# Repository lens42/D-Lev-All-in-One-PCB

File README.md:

# D-Lev-All-in-One-PCB
This integrates the excellent D-Lev digital theremin design at D-Lev.com into a single surface-mount PCB.

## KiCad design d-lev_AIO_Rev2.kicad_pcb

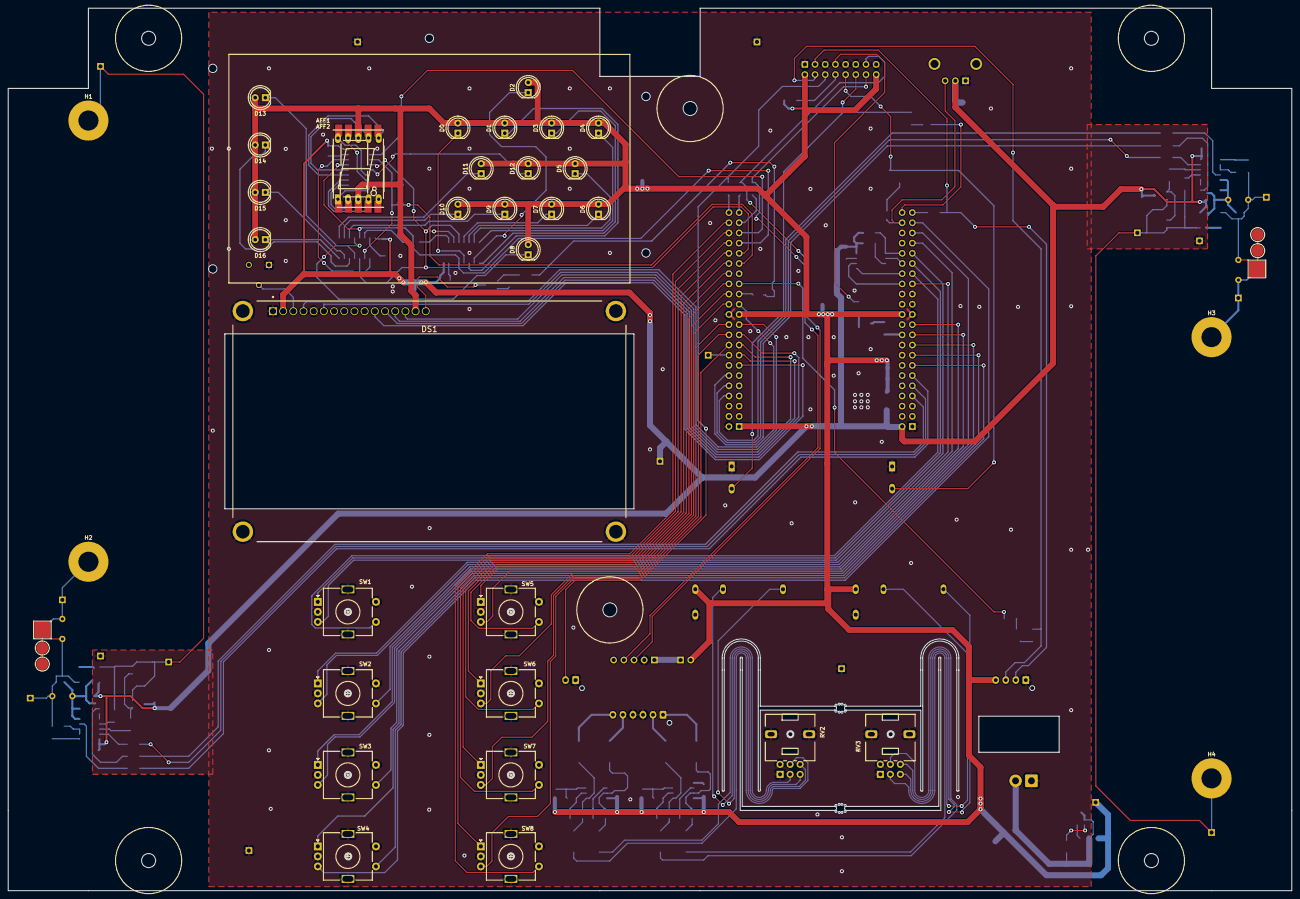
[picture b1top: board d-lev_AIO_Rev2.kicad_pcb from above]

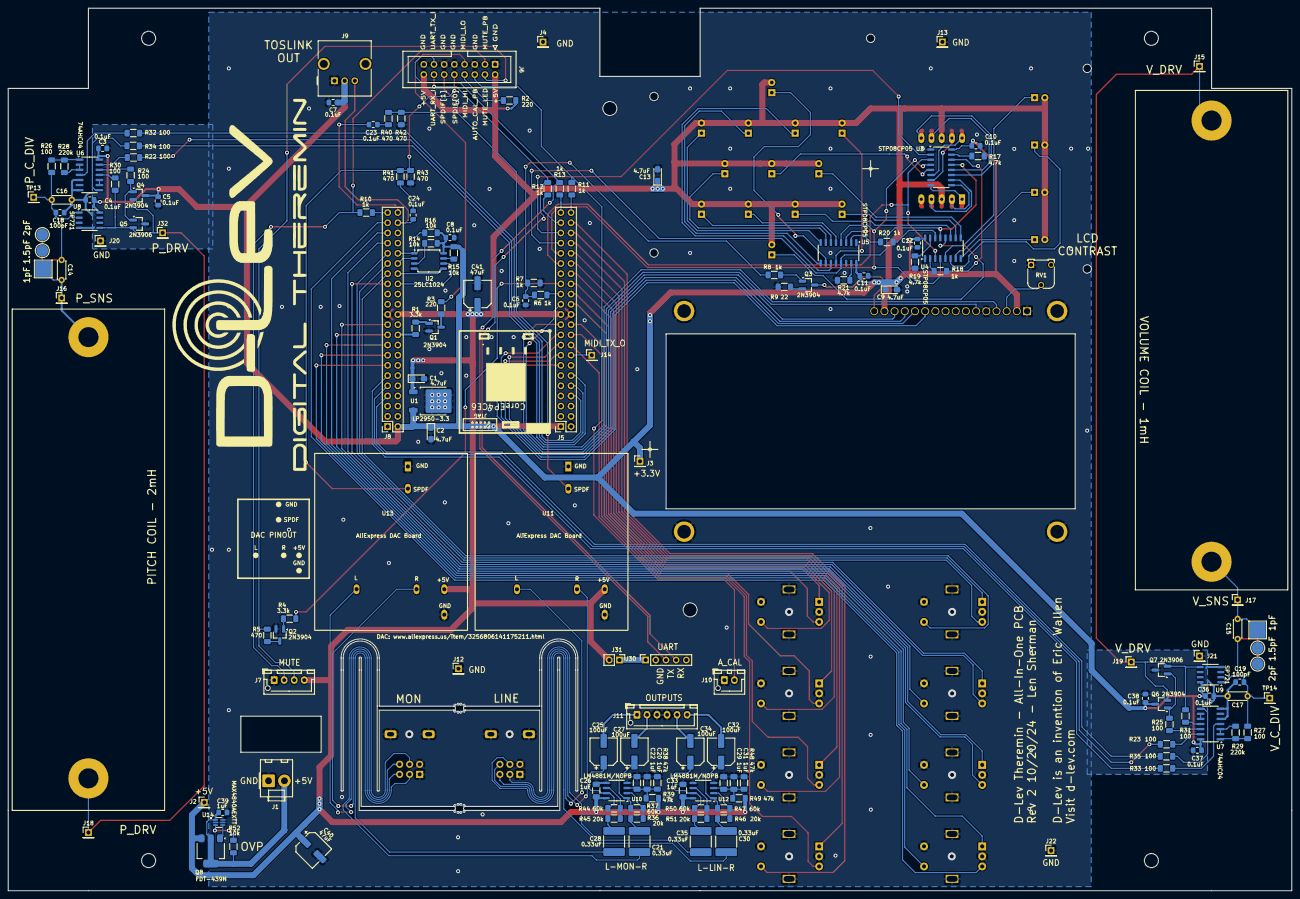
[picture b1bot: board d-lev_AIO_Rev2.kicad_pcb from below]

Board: 2 copper layers, 320.0 x 220.0 mm, 191 parts (149 on the bottom side), 165 nets.

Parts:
AFF1: LTS-6960HR; 7SEGMENT-LED__HDSM531_HDSM533_SMD
AFF2: LTS-6960HR; 7SegmentLED_LTS6760_LTS6780-centered
C1, C2, C9, C13: 4.7uF; CP_EIA-3216-18_Kemet-A_Pad1.58x1.35mm_HandSolder
C3, C4, C5, C6, C7, C8, C10, C11, C12, C23, C24, C36, C37, C38: 0.1uF; C_0805_2012Metric_Pad1.18x1.45mm_HandSolder
C14, C15: 1pF; C_Disc_D4.3mm_W1.9mm_P5.00mm
C16, C17: 100pF; C_Disc_D4.3mm_W1.9mm_P5.00mm
C18, C19: 100pF; C_0805_2012Metric_Pad1.18x1.45mm_HandSolder
C20, C22, C26, C29, C31, C33: 1uF; C_1206_3216Metric_Pad1.33x1.80mm_HandSolder
C21, C28, C30, C35: 0.33uF; C_2220_5750Metric_Pad1.97x5.40mm_HandSolder
C25, C27, C32, C34: 100uF; CP_Elec_6.3x7.7
C39: 1uF; C_0805_2012Metric_Pad1.18x1.45mm_HandSolder
C40, C41: 47uF; CP_Elec_6.3x7.7
D0, D1, D2, D3, D4, D5, D6, D7, D8, D9, D10, D11, D12, D13, D14, D15, D16: LED; LED_D5.0mm flush mounted
DS1: LCD-20X4B; LCD_LCD-20X4B
H1, H2, H3, H4: MountingHole_Pad; MountingHole_5mm_Pad
J1: Conn_01x02_Male; Molex_KK-396_A-41791-0002_1x02_P3.96mm_Vertical
J2, J3, J4, J12, J13, J22: Conn_01x01_Pin; PinHeader_1x01_P2.54mm_Vertical
J5, J8: Conn_02x22_Odd_Even; PinSocket_2x22_P2.54mm_Vertical
J6: Conn_02x08_Odd_Even; IDC-Header_2x08_P2.54mm_Vertical
J7: Conn_01x04_Pin; JST_XH_B4B-XH-AM_1x04_P2.50mm_Vertical
J9: TOSLINK_TX
J10: Conn_01x02_Pin; JST_XH_B2B-XH-AM_1x02_P2.50mm_Vertical
J11: Conn_01x06_Pin; JST_XH_B6B-XH-AM_1x06_P2.50mm_Vertical
J14, J15, J16, J17, J18, J19, J20, J21, J32: Conn_01x01_Male; PinHeader_1x01_P2.54mm_Vertical
J30: Conn_01x05_Pin; PinSocket_1x05_P2.54mm_Vertical
J31: Conn_01x02; PinHeader_1x02_P2.54mm_Vertical
Q1, Q2, Q3, Q4, Q6: 2N3904; SOT-23_Handsoldering
Q5, Q7: 2N3906; SOT-23_Handsoldering
Q8: FDT-439N; SOT-223-3_TabPin2
R1, R4: 3.3k; R_1206_3216Metric_Pad1.30x1.75mm_HandSolder
R2, R3: 220; R_1206_3216Metric_Pad1.30x1.75mm_HandSolder
R5, R40, R41, R42, R43: 470; R_1206_3216Metric_Pad1.30x1.75mm_HandSolder
R6, R7, R8, R10, R11, R12, R13, R18, R20: 1k; R_1206_3216Metric_Pad1.30x1.75mm_HandSolder
R9: 22; R_1206_3216Metric_Pad1.30x1.75mm_HandSolder
R14, R15, R16, R52: 10k; R_1206_3216Metric_Pad1.30x1.75mm_HandSolder
R17, R19, R21: 4.7k; R_1206_3216Metric_Pad1.30x1.75mm_HandSolder
R22, R23, R24, R25, R26, R27, R30, R31, R32, R33, R34, R35: 100; R_1206_3216Metric_Pad1.30x1.75mm_HandSolder
R28, R29: 220k; R_1206_3216Metric_Pad1.30x1.75mm_HandSolder
R36, R45, R46, R51: 20k; R_1206_3216Metric_Pad1.30x1.75mm_HandSolder
R37, R44, R47, R50: 60k; R_1206_3216Metric_Pad1.30x1.75mm_HandSolder
R38, R39, R48, R49: 47k; R_1206_3216Metric_Pad1.30x1.75mm_HandSolder
RV1: R_POT_US; Potentiometer_Runtron_RM-065_Vertical
RV2, RV3: 10k pot; Potentiometer_Alps_RK09L_Double_Vertical - recentered
SW1, SW2, SW3, SW4, SW5, SW6, SW7, SW8: RotaryEncoder_Switch_MP; RotaryEncoder_Alps_EC11E-Switch_Vertical_H20mm w 3D
TP1, TP2, TP3, TP4, TP5, TP6, TP9, TP10: TestPoint; TestPoint_Pad_D3.0mm
TP7, TP8, TP11, TP12: TestPoint; TestPoint_Pad_4.0x4.0mm
TP13, TP14: TestPoint; PinHeader_1x01_P2.54mm_Vertical
U1: LP2950-3.3; TO-252-2
U2: 25LC1024; SO-8_25LC1024_EEPROM
U3, U4, U5: STP08CP05; SO-16_3.9x9.9mm_P1.27mm
U6, U7: 74AHC04; SO-14_3.9x8.65mm_P1.27mm
U8, U9: SP721; SO-8_3.9x4.9mm_P1.27mm
U10, U12: LM4881M/NOPB; SO-8_3.9x4.9mm_P1.27mm
U11, U13: Audio DAC Brd
U14: MAX4840AEXTT; SOT65P210X110-6N
mouse-bite-1mm-slot, mouse-bite-1mm-slot#2: VAL**; mouse-bite-1mm-slot

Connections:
+3V3: C2.1, C3.1, C4.1, C5.1, C7.1, C8.1, C9.1, C10.1, C11.1, C12.1, C36.1, C37.1, C38.1, DS1.2 (VDD), J3.1, J5.1, J8.2, J9.2 (VCC), Q4.3 (C), Q6.3 (C), R14.2, R15.2, R16.1, U1.3 (VO), U2.8 (VCC), U3.16 (VDD), U4.16 (VDD), U5.16 (VDD), U6.14 (VCC), U7.14 (VCC), U8.8 (VCC), U9.8 (VCC)
+5V: AFF1.3 (C.A.), AFF1.8 (C.A.), AFF2.3 (C.A.), AFF2.8 (C.A.), C1.1, C13.1, C26.2, C33.2, C40.1, C41.1, D0.2 (A), D1.2 (A), D2.2 (A), D3.2 (A), D4.2 (A), D5.2 (A), D6.2 (A), D7.2 (A), D8.2 (A), D9.2 (A), D10.2 (A), D11.2 (A), D12.2 (A), D13.2 (A), D14.2 (A), D15.2 (A), D16.2 (A), DS1.15 (A), J2.1, J5.23, J6.2, J6.16, J7.4, J8.24, J31.2, Q8.3 (S), R2.2, R39.2, R49.2, U1.1 (VI), U10.8 (VDD), U11.5 (DC_5V), U12.8 (VDD), U13.5 (DC_5V)
/acal_pb: J6.6, J10.2, R11.1
/pb_mute_pu: J6.3, J7.2, R10.2
A: AFF1.7 (a), AFF2.7 (a), U3.12 (OUT7)
A0: J8.33, SW1.A
A1: J8.29, SW2.A
A2: J8.19, SW3.A
A3: J8.15, SW4.A
A4: J5.28, SW5.A
A5: J5.32, SW6.A
A6: J5.36, SW7.A
A7: J5.40, SW8.A
B: AFF1.6 (b), AFF2.6 (b), U3.11 (OUT6)
B0: J8.35, SW1.B
B1: J8.37, SW2.B
B2: J8.39, SW3.B
B3: J8.41, SW4.B
B4: J5.26, SW5.B
B5: J5.22, SW6.B
B6: J5.20, SW7.B
B7: J5.18, SW8.B
C: AFF1.4 (c), AFF2.4 (c), U3.10 (OUT5)
D: AFF1.2 (d), AFF2.2 (d), U3.9 (OUT4)
E: AFF1.1 (e), AFF2.1 (e), U3.8 (OUT3)
F: AFF1.9 (f), AFF2.9 (f), U3.7 (OUT2)
G: AFF1.10 (g), AFF2.10 (g), U3.6 (OUT1)
GND: C1.2, C2.2, C3.2, C4.2, C5.2, C6.2, C7.2, C8.2, C9.2, C10.2, C11.2, C12.2, C13.2, C16.2, C17.2, C18.2, C19.2, C20.1, C22.1, C26.1, C29.1, C31.1, C33.1, C36.2, C37.2, C38.2, C39.2, C40.2, C41.2, DS1.1 (VSS), DS1.5 (R/W), DS1.S1 (SHIELD), DS1.S2 (SHIELD), DS1.S3 (SHIELD), DS1.S4 (SHIELD), J1.1, J4.1, J5.2, J5.24, J6.1, J6.5, J6.9, J6.11, J6.15, J7.1, J8.1, J8.23, J9.1 (GND), J10.1, J11.3, J11.4, J12.1, J13.1, J20.1, J21.1, J22.1, J30.2, Q1.2 (E), Q2.2 (E), Q5.3 (C), Q7.3 (C), R7.2, R9.1, R17.2, R19.2, R21.2, R38.2, R42.2, R43.2, R48.2, RV1.1, RV2.1, RV2.4, RV2.MP (MountPin), RV3.1, RV3.4, RV3.MP (MountPin), SW1.C, SW1.MP, SW1.S2, SW2.C, SW2.MP, SW2.S2, SW3.C, SW3.MP, SW3.S2, SW4.C, SW4.MP, SW4.S2, SW5.C, SW5.MP, SW5.S2, SW6.C, SW6.MP, SW6.S2, SW7.C, SW7.MP, SW7.S2, SW8.C, SW8.MP, SW8.S2, U1.2 (GND), U2.4 (GND), U3.1 (GND), U4.1 (GND), U5.1 (GND), U6.5, U6.7 (GND), U7.5, U7.7 (GND), U8.4 (GND), U9.4 (GND), U10.4 (GND), U10.5 (SD), U11.1 (GND), U11.6 (GND), U12.4 (GND), U12.5 (SD), U13.1 (GND), U13.6 (GND), U14.2 (GND), U14.5 (NC), U14.6 (~EN)
LED0: D0.1 (K), U5.12 (OUT7)
LED1: D1.1 (K), U5.11 (OUT6)
LED2: D2.1 (K), U5.10 (OUT5)
LED3: D3.1 (K), U5.9 (OUT4)
LED4: D4.1 (K), U5.8 (OUT3)
LED5: D5.1 (K), U5.7 (OUT2)
LED6: D6.1 (K), U5.6 (OUT1)
LED7: D7.1 (K), U5.5 (OUT0)
LED8: D8.1 (K), U4.12 (OUT7)
LED9: D9.1 (K), U4.11 (OUT6)
LED10: D10.1 (K), U4.10 (OUT5)
LED11: D11.1 (K), U4.9 (OUT4)
LED12: D12.1 (K), U3.5 (OUT0)
LED13: D13.1 (K), U4.5 (OUT0)
LED14: D14.1 (K), U4.6 (OUT1)
LED15: D15.1 (K), U4.7 (OUT2)
LED16: D16.1 (K), U4.8 (OUT3)
LINE_L_AMP_IN: C30.2, RV2.5
LINE_L_DAC: RV2.6, U11.3 (LEFT_OUT)
LINE_R_AMP_IN: C35.1, RV2.2
LINE_R_DAC: RV2.3, U11.4 (RIGHT_OUT)
LIN_L_OUT: C32.2, J11.6
LIN_R_OUT: C34.2, J11.5
MON_L_AMP_IN: C21.2, RV3.5
MON_L_DAC: RV3.6, U13.3 (LEFT_OUT)
MON_L_OUT: C27.2, J11.2
MON_R_AMP_IN: C28.2, RV3.2
MON_R_DAC: RV3.3, U13.4 (RIGHT_OUT)
MON_R_OUT: C25.2, J11.1
unnamed: AFF1.5 (DP), AFF2.5 (DP)
unnamed: C6.1, R6.1, R7.1, R8.2
unnamed: C21.1, R36.2
unnamed: C23.2, R40.2
unnamed: C24.2, R41.2
unnamed: C28.1, R45.1
unnamed: C30.1, R46.2
unnamed: C35.2, R51.1
unnamed: C39.1, J1.2, Q8.2 (D), R52.2, U14.1 (IN)
unnamed: C14.1, H3.1, J16.1, TP7.1
unnamed: C15.1, H2.1, J17.1, TP8.1
unnamed: J30.1, J31.1
unnamed: J6.13, J30.3, R13.2
unnamed: J6.14, J30.4, R12.1
unnamed: Q1.1 (B), R1.1
unnamed: Q1.3 (C), R3.2
unnamed: Q2.1 (B), R4.1
unnamed: Q2.3 (C), R5.2
unnamed: Q3.1 (B), R8.1
unnamed: Q3.2 (E), R9.2
unnamed: Q4.1 (B), Q5.1 (B), R24.1
unnamed: Q6.1 (B), Q7.1 (B), R25.1
unnamed: Q8.1 (G), U14.4 (GATE)
unnamed: R22.1, U6.13
unnamed: R23.1, U7.13
unnamed: R24.2, U6.12
unnamed: R25.2, U7.12
unnamed: R26.1, R28.2, U6.1
unnamed: R27.1, R29.2, U7.1
unnamed: R28.1, U6.2, U6.3
unnamed: R29.1, U7.2, U7.3
unnamed: R30.1, U6.11
unnamed: R31.1, U7.11
unnamed: R32.2, U6.4
unnamed: R33.2, U7.4
unnamed: R34.2, U6.8
unnamed: R35.2, U7.8
unnamed: R15.1, U2.7 (~HOLD)
unnamed: R14.1, U2.3 (~WP)
unnamed: R17.1, U3.15 (R-EXT)
unnamed: R18.2, U3.14 (SDO)
unnamed: R19.1, U4.15 (R-EXT)
unnamed: R18.1, U4.2 (SDI)
unnamed: R20.2, U4.14 (SDO)
unnamed: R21.1, U5.15 (R-EXT)
unnamed: R20.1, U5.2 (SDI)
unnamed: U6.9, U6.10
unnamed: U7.9, U7.10
unnamed: C20.2, C22.2, R38.1, R39.1, U10.3 (BYPASS)
unnamed: R36.1, R37.2, U10.2 (IN_A)
unnamed: R44.2, R45.2, U10.6 (IN_B)
unnamed: C27.1, R37.1, U10.1 (OUT_A)
unnamed: C25.1, R44.1, U10.7 (OUT_B)
unnamed: C29.2, C31.2, R48.1, R49.1, U12.3 (BYPASS)
unnamed: R46.1, R47.2, U12.2 (IN_A)
unnamed: R50.2, R51.2, U12.6 (IN_B)
unnamed: C32.1, R47.1, U12.1 (OUT_A)
unnamed: C34.1, R50.1, U12.7 (OUT_B)
unnamed: R52.1, U14.3 (~FLAG)
P_C_DIV: C14.2, C16.1, C18.1, R26.2, TP3.1, TP9.1, TP11.1, TP13.1, U8.1 (K1)
P_L_OUT: H4.1, J18.1, J32.1, Q4.2 (E), Q5.2 (E), R30.2, U8.5 (K4)
P_QUAD: J5.8, R32.1
P_SQ: J5.10, R22.2
P_ZERO: J5.12, R34.1
S0: J8.31, SW1.S1
S1: J8.21, SW2.S1
S2: J8.17, SW3.S1
S3: J8.13, SW4.S1
S4: J5.30, SW5.S1
S5: J5.34, SW6.S1
S6: J5.38, SW7.S1
S7: J5.42, SW8.S1
TUN_CLK: J5.33, U3.3 (CLK), U4.3 (CLK), U5.3 (CLK)
TUN_LE: J5.35, U3.4 (LE), U4.4 (LE), U5.4 (LE)
TUN_OE: J5.37, U3.13 (~OE), U4.13 (~OE), U5.13 (~OE)
TUN_SDI: J5.39, U3.2 (SDI)
V_C_DIV: C15.2, C17.1, C19.1, R27.2, TP6.1, TP10.1, TP12.1, TP14.1, U9.1 (K1)
V_L_OUT: H1.1, J15.1, J19.1, Q6.2 (E), Q7.2 (E), R31.2, U9.5 (K4)
V_QUAD: J8.11, R33.1
V_SQ: J8.9, R23.2
V_ZERO: J8.7, R35.1
lcd_cathode: DS1.16 (K), Q3.3 (C)
lcd_contrast: DS1.3 (V0), RV1.2
lcd_data_o[0]: DS1.11 (DB4), J5.13
lcd_data_o[1]: DS1.12 (DB5), J5.19
lcd_data_o[2]: DS1.13 (DB6), J5.15
lcd_data_o[3]: DS1.14 (DB7), J5.17
lcd_e_o: DS1.6 (E), J5.21
lcd_pwm_o: J5.27, R6.2
lcd_rs_o: DS1.4 (RS), J5.25
midi_hi: J6.8, R2.1
midi_lo: J6.7, R3.1
midi_tx_n_o: J8.20, R1.2
midi_tx_o: J5.16, J14.1
mute_led_n: J6.4, J7.3, R5.1
mute_led_o: J5.29, R4.2
pb_acal_i: J5.44, R11.2
pb_mute_i: J8.43, R10.1
spdif[0]: J6.10, R41.1, R43.1, U13.2 (SPIF_IN)
spdif[1]: J6.12, R40.1, R42.1, U11.2 (SPIF_IN)
spdif_tx_o[0]: C24.1, J8.42, J9.3 (Data_in)
spdif_tx_o[1]: C23.1, J8.44
spi_scl_o: J8.30, U2.6 (SCK)
spi_scs_o: J8.36, R16.2, U2.1 (~CS)
spi_sdi_o: J8.32, U2.5 (MOSI)
spi_sdo_i: J8.34, U2.2 (MISO)
uart_rx_i: J5.41, R12.2
uart_tx_o: J5.43, R13.1
